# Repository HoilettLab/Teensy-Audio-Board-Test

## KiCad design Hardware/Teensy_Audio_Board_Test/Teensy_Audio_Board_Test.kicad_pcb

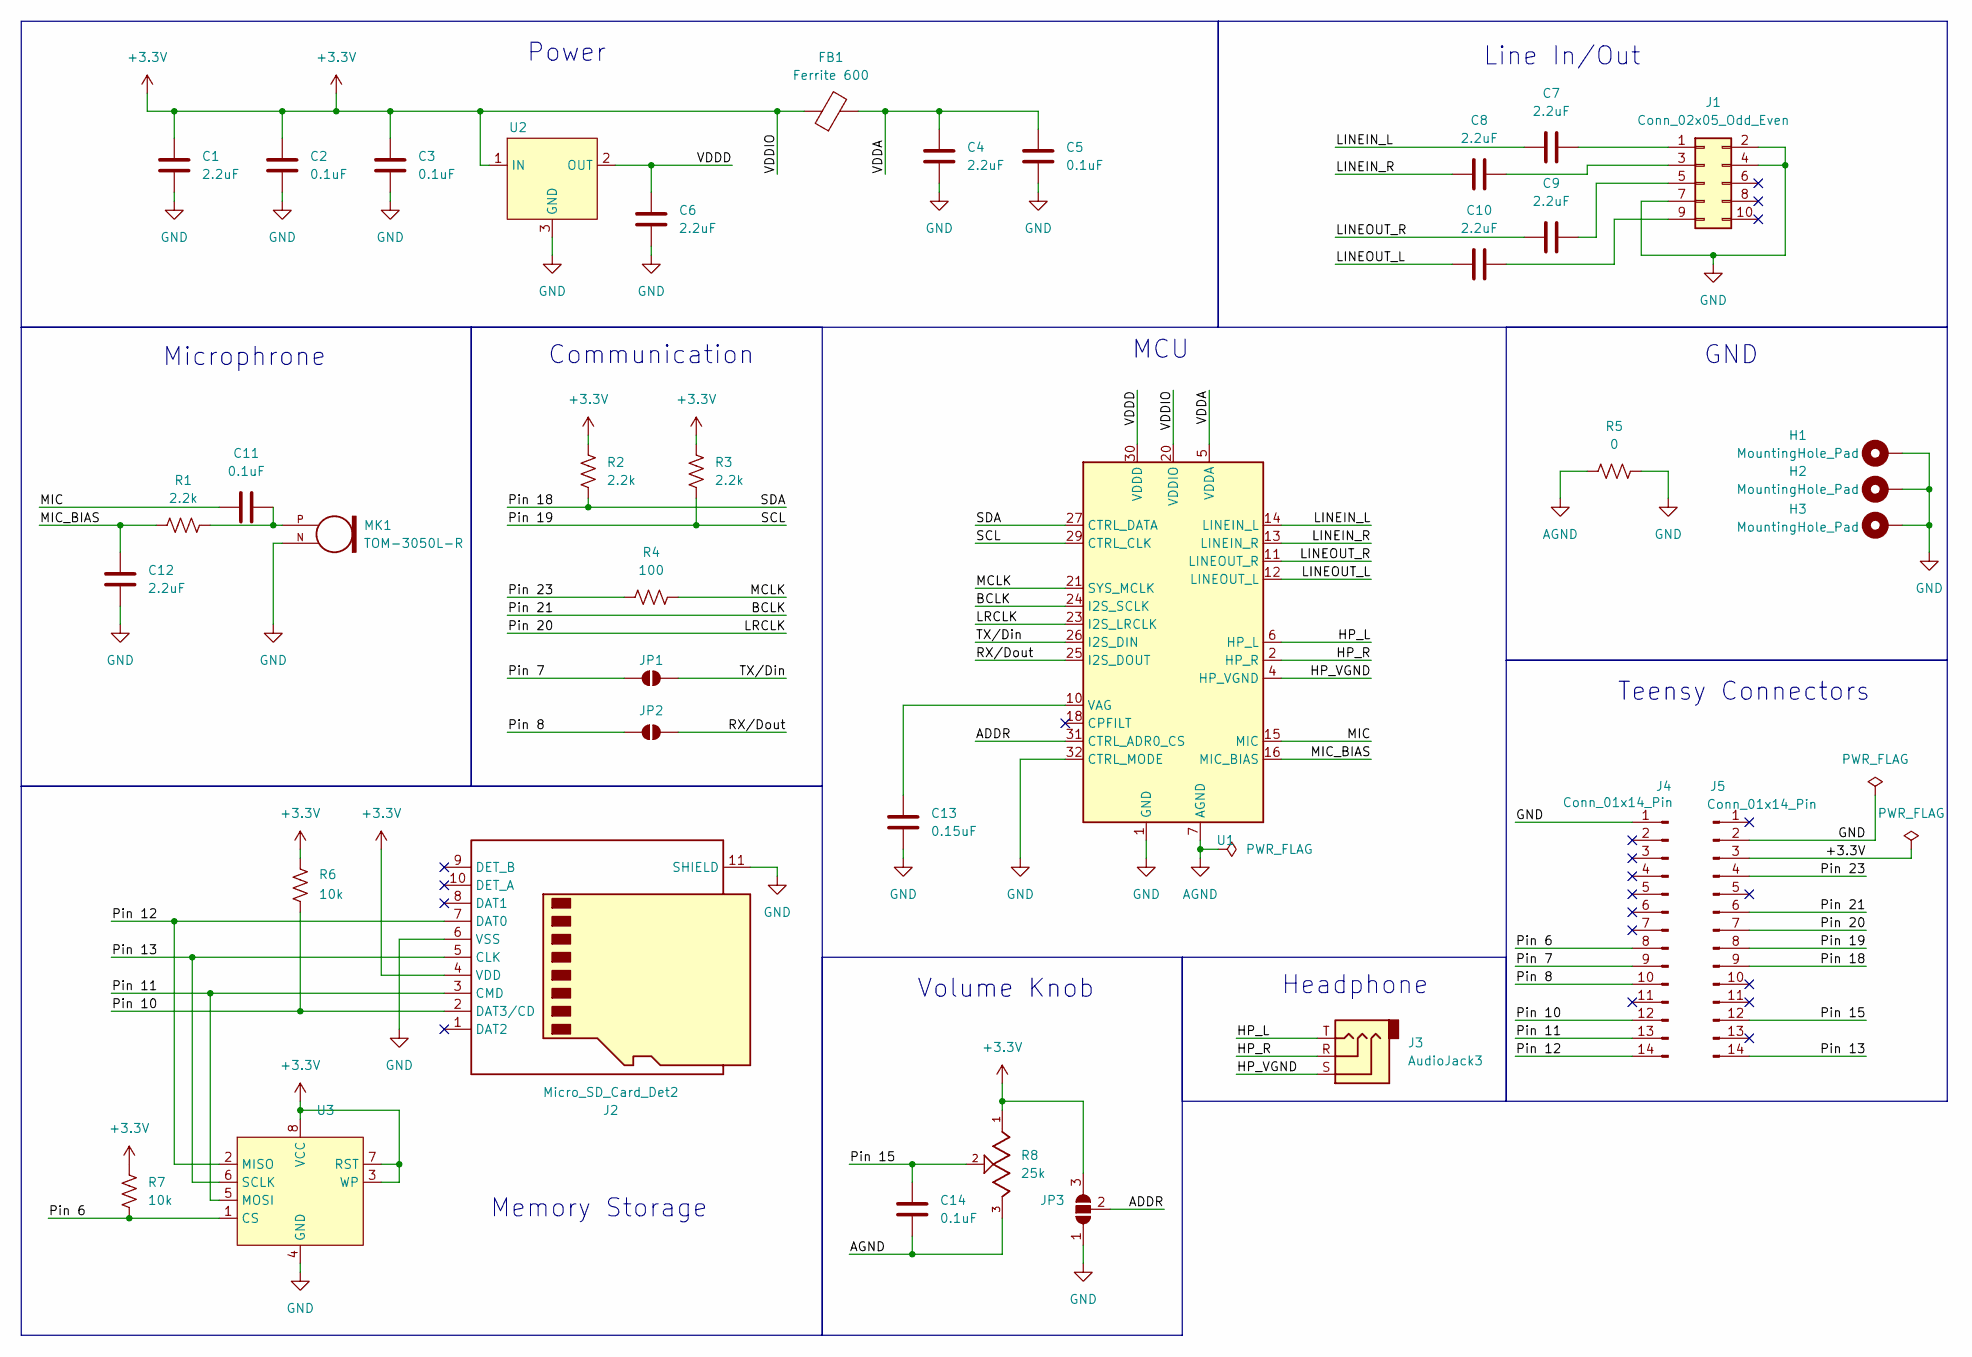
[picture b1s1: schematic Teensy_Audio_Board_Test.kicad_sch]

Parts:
C1, C4, C6, C7, C8, C9, C10, C12: 2.2uF; C_0402_1005Metric
C2, C3, C5, C11, C14: 0.1uF; C_0402_1005Metric
C13: 0.15uF; C_0402_1005Metric
FB1: Ferrite 600; L_0402_1005Metric
H1, H2, H3: MountingHole_Pad; MountingHole_3.2mm_M3_ISO7380_Pad
J1: Conn_02x05_Odd_Even; PinHeader_2x05_P2.54mm_Vertical
J2: Micro_SD_Card_Det2; microSD_HC_Hirose_DM3D-SF
J3: AudioJack3; Jack_3.5mm_CUI_SJ-3523-SMT_Horizontal
J4, J5: Conn_01x14_Pin; PinHeader_1x14_P2.54mm_Vertical
JP1, JP2: SolderJumper_2_Open; SolderJumper-2_P1.3mm_Open_Pad1.0x1.5mm
JP3: SolderJumper_3_Open; SolderJumper-3_P1.3mm_Open_Pad1.0x1.5mm
MK1: TOM-3050L-R; MIC_TOM-3050L-R; PARTREV A
R1, R2, R3: 2.2k; R_0402_1005Metric
R4: 100; R_0402_1005Metric
R5: 0; R_0402_1005Metric
R6, R7: 10k; R_0402_1005Metric
R8: 25k; TRIM_3352T-1-253LF; PARTREV 08/19
U1: QFN-32-1EP_5x5mm_P0.5mm_EP3.6x3.6mm
U2: SOT95P260X110-3N
U3: SOIC127P600X175-8N

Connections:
+3.3V: C1.1, C2.1, C3.1, FB1.1, J2.4 (VDD), J5.3, JP3.3 (B), R2.2, R3.2, R6.1, R7.1, R8.1, U1.20 (VDDIO), U2.1 (IN), U3.3 (WP), U3.7 (RST), U3.8 (VCC)
/ADDR: JP3.2 (C), U1.31 (CTRL_ADR0_CS)
/BCLK: J5.6, U1.24 (I2S_SCLK)
/HP_L: J3.T, U1.6 (HP_L)
/HP_R: J3.R, U1.2 (HP_R)
/HP_VGND: J3.S, U1.4 (HP_VGND)
/LINEIN_L: C7.1, U1.14 (LINEIN_L)
/LINEIN_R: C8.1, U1.13 (LINEIN_R)
/LINEOUT_L: C10.1, U1.12 (LINEOUT_L)
/LINEOUT_R: C9.1, U1.11 (LINEOUT_R)
/LRCLK: J5.7, U1.23 (I2S_LRCLK)
/MCLK: R4.2, U1.21 (SYS_MCLK)
/MIC: C11.1, U1.15 (MIC)
/MIC_BIAS: C12.2, R1.1, U1.16 (MIC_BIAS)
/Pin 6: J4.8, R7.2, U3.1 (CS)
/Pin 7: J4.9, JP1.1 (A)
/Pin 8: J4.10, JP2.1 (A)
/Pin 10: J2.2 (DAT3/CD), J4.12, R6.2
/Pin 11: J2.3 (CMD), J4.13, U3.5 (MOSI)
/Pin 12: J2.7 (DAT0), J4.14, U3.2 (MISO)
/Pin 13: J2.5 (CLK), J5.14, U3.6 (SCLK)
/Pin 15: C14.2, J5.12, R8.2
/Pin 18: J5.9, R2.1, U1.27 (CTRL_DATA)
/Pin 19: J5.8, R3.1, U1.29 (CTRL_CLK)
/Pin 23: J5.4, R4.1
/RX/Dout: JP2.2 (B), U1.25 (I2S_DOUT)
/TX/Din: JP1.2 (B), U1.26 (I2S_DIN)
/VDDA: C4.1, C5.1, FB1.2, U1.5 (VDDA)
/VDDD: C6.1, U1.30 (VDDD), U2.2 (OUT)
AGND: C14.1, R5.1, R8.3, U1.7 (AGND)
GND: C1.2, C2.2, C3.2, C4.2, C5.2, C6.2, C12.1, C13.1, H1.1, H2.1, H3.1, J1.2, J1.4, J1.7, J2.6 (VSS), J2.11 (SHIELD), J4.1, J5.2, JP3.1 (A), MK1.N, R5.2, U1.1 (GND), U1.3 (GND), U1.32 (CTRL_MODE), U1.33 (GND), U2.3 (GND), U3.4 (GND)
unnamed: C11.2, MK1.P, R1.2
unnamed: C7.2, J1.1
unnamed: C8.2, J1.3
unnamed: C9.2, J1.5
unnamed: C10.2, J1.9
unnamed: C13.2, U1.10 (VAG)

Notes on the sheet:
Microphrone
Volume Knob
Headphone
Power
Memory Storage
Teensy Connectors
MCU
Communication
GND
Line In/Out

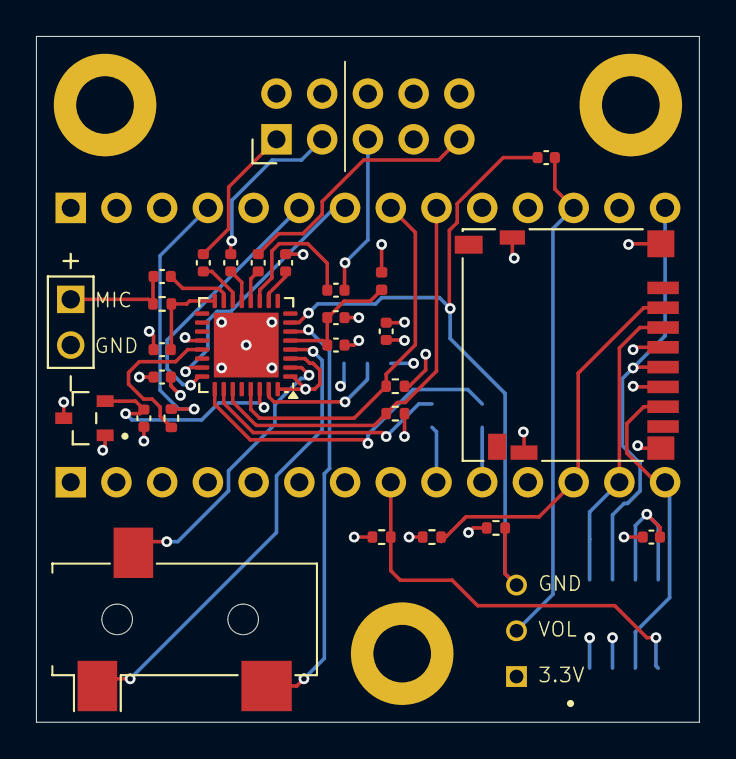
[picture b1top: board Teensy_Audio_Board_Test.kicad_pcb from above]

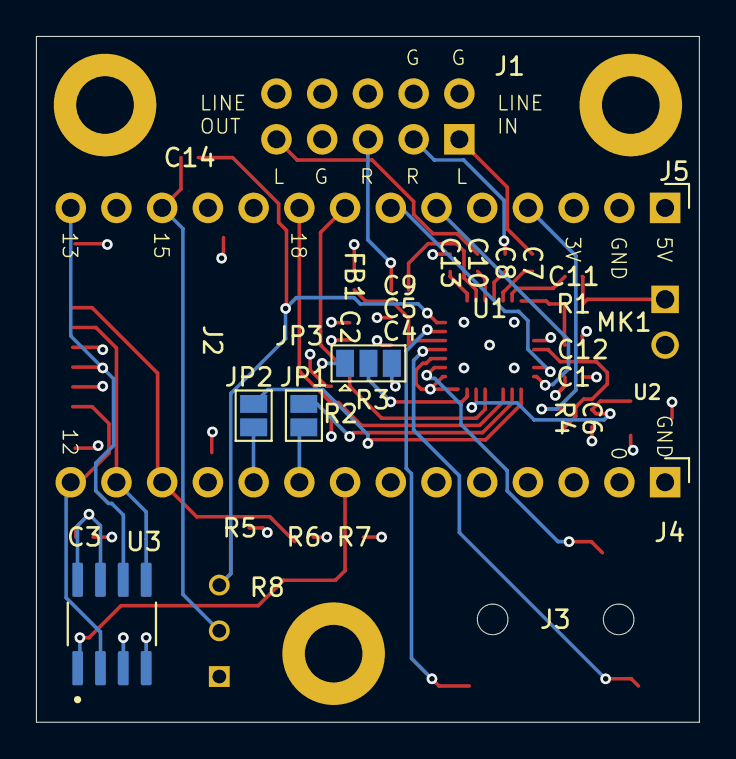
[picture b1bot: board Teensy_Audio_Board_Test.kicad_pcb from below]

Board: 4 copper layers, 36.8 x 38.1 mm, 38 parts (6 on the bottom side), 37 nets.

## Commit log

2024-07-25 initial cmmit
2025-03-04 Add schematic and board KiCad documents
2025-03-04 Adding BOM
2025-03-04 Adding KiCad project files
2025-03-11 Finalizing DRC Edits
